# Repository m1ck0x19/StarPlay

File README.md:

# StarPlay
Its a simple star shaped device that sits on your desk and plays music through your computer when you push a button

So, im finally done, I ended up making the PCB as a rectangle and im panning on designing a 3D printed enclosure for it, as soon as I do, ill upload the files over here, it features an ESP32-c3 supermini, that comes with bluetooth and wifi, The screen is 1.28 inch LCD TFT display with a simple 6mm tactile button, when you press the button it runs a shortcut to your computer that opens up Spotify or another music playing app.

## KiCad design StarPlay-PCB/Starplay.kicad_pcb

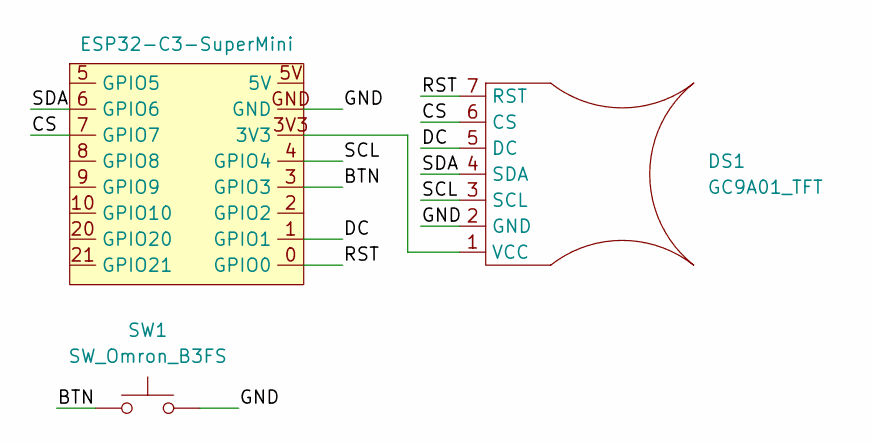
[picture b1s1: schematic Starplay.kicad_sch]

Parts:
DS1: GC9A01_TFT; GC9A01 TFT
SW1: SW_Omron_B3FS; SW_PUSH_6mm
U1: ESP32-C3-SuperMini

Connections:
/BTN: SW1.1, U1.3 (GPIO3)
/CS: DS1.6 (CS), U1.7 (GPIO7)
/DC: DS1.5 (DC), U1.1 (GPIO1)
/GND: DS1.2 (GND), SW1.2, U1.GND
/RST: DS1.7 (RST), U1.0 (GPIO0)
/SCL: DS1.3 (SCL), U1.4 (GPIO4)
/SDA: DS1.4 (SDA), U1.6 (GPIO6)
unnamed: DS1.1 (VCC), U1.3V3

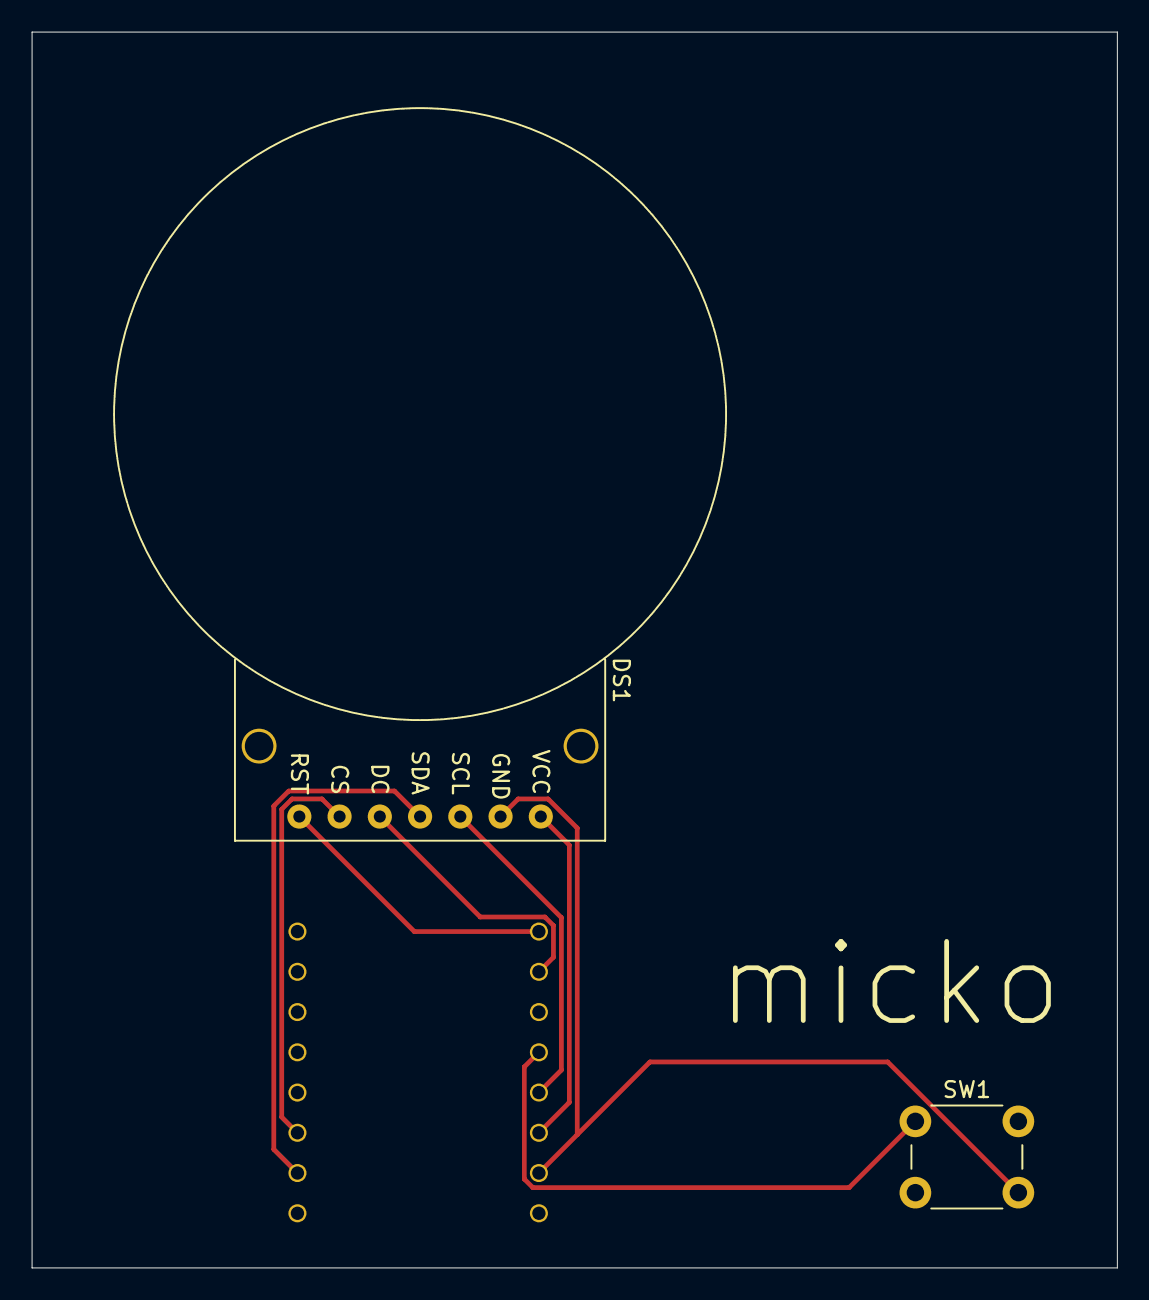
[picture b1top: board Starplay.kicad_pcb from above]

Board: 2 copper layers, 68.5 x 78.0 mm, 3 parts (1 on the bottom side), 8 nets.
